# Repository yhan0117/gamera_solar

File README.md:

<!--
Hey, thanks for using the awesome-readme-template template.  
If you have any enhancements, then fork this project and create a pull request 
or just open an issue with the label "enhancement".

Don't forget to give this project a star for additional support ;)
Maybe you can mention me or this repo in the acknowledgements too
-->
<div align="center">

  <h1>Gamera Solar</h1>
  
  <p>
    An awesome README template for your projects! 
  </p>

<!-- Badges -->

<!-- Table of Contents -->
# :notebook_with_decorative_cover: Table of Contents

- [About the Project](#star2-about-the-project)
  * [Screenshots](#camera-screenshots)
  * [Tech Stack](#space_invader-tech-stack)
  * [Features](#dart-features)
  * [Color Reference](#art-color-reference)
  * [Environment Variables](#key-environment-variables)
- [Getting Started](#toolbox-getting-started)
  * [Prerequisites](#bangbang-prerequisites)
  * [Installation](#gear-installation)
  * [Running Tests](#test_tube-running-tests)
  * [Run Locally](#running-run-locally)
  * [Deployment](#triangular_flag_on_post-deployment)
- [Usage](#eyes-usage)
- [Roadmap](#compass-roadmap)
- [Contributing](#wave-contributing)
  * [Code of Conduct](#scroll-code-of-conduct)
- [FAQ](#grey_question-faq)
- [License](#warning-license)
- [Contact](#handshake-contact)
- [Acknowledgements](#gem-acknowledgements)

<!-- About the Project -->
## :star2: About the Project

<!-- Screenshots -->
### :camera: Screenshots

<div align="center"> 
  
</div>

<!-- TechStack -->
### :space_invader: Tech Stack

<details>
  <summary>Client</summary>
  <ul>
    <li><a href="https://www.typescriptlang.org/">Typescript</a></li>
    <li><a href="https://nextjs.org/">Next.js</a></li>
    <li><a href="https://reactjs.org/">React.js</a></li>
    <li><a href="https://tailwindcss.com/">TailwindCSS</a></li>
  </ul>
</details>

<details>
  <summary>Server</summary>
  <ul>
    <li><a href="https://www.typescriptlang.org/">Typescript</a></li>
    <li><a href="https://expressjs.com/">Express.js</a></li>
    <li><a href="https://go.dev/">Golang</a></li>
    <li><a href="https://nestjs.com/">Nest.js</a></li>
    <li><a href="https://socket.io/">SocketIO</a></li>
    <li><a href="https://www.prisma.io/">Prisma</a></li>    
    <li><a href="https://www.apollographql.com/">Apollo</a></li>
    <li><a href="https://graphql.org/">GraphQL</a></li>
  </ul>
</details>

<details>
<summary>Database</summary>
  <ul>
    <li><a href="https://www.mysql.com/">MySQL</a></li>
    <li><a href="https://www.postgresql.org/">PostgreSQL</a></li>
    <li><a href="https://redis.io/">Redis</a></li>
    <li><a href="https://neo4j.com/">Neo4j</a></li>
    <li><a href="https://www.mongodb.com/">MongoDB</a></li>
  </ul>
</details>

<details>
<summary>DevOps</summary>
  <ul>
    <li><a href="https://www.docker.com/">Docker</a></li>
    <li><a href="https://www.jenkins.io/">Jenkins</a></li>
    <li><a href="https://circleci.com/">CircleCLI</a></li>
  </ul>
</details>

<!-- Features -->
### :dart: Features

- Feature 1
- Feature 2
- Feature 3

<!-- Color Reference -->
### :art: Color Reference

| Color             | Hex                                                                |
| ----------------- | ------------------------------------------------------------------ |
| Primary Color |  #222831 |
| Secondary Color |  #393E46 |
| Accent Color |  #00ADB5 |
| Text Color |  #EEEEEE |

<!-- Env Variables -->
### :key: Environment Variables

To run this project, you will need to add the following environment variables to your .env file

`API_KEY`

`ANOTHER_API_KEY`

<!-- Getting Started -->
## 	:toolbox: Getting Started

<!-- Prerequisites -->
### :bangbang: Prerequisites

This project uses Yarn as package manager

```bash
 npm install --global yarn
```

<!-- Installation -->
### :gear: Installation

Install my-project with npm

```bash
  yarn install my-project
  cd my-project
```
   
<!-- Running Tests -->
### :test_tube: Running Tests

To run tests, run the following command

```bash
  yarn test test
```

<!-- Run Locally -->
### :running: Run Locally

Clone the project

```bash
  git clone https://github.com/Louis3797/awesome-readme-template.git
```

Go to the project directory

```bash
  cd my-project
```

Install dependencies

```bash
  yarn install
```

Start the server

```bash
  yarn start
```

<!-- Deployment -->
### :triangular_flag_on_post: Deployment

To deploy this project run

```bash
  yarn deploy
```

<!-- Usage -->
## :eyes: Usage

Use this space to tell a little more about your project and how it can be used. Show additional screenshots, code samples, demos or link to other resources.

```javascript
import Component from 'my-project'

function App() {
  return <Component />
}
```

<!-- Roadmap -->
## :compass: Roadmap

* [x] Todo 1
* [ ] Todo 2

<!-- Contributing -->
## :wave: Contributing

Contributions are always welcome!

See `contributing.md` for ways to get started.

<!-- Code of Conduct -->
### :scroll: Code of Conduct

Please read the [Code of Conduct](https://github.com/Louis3797/awesome-readme-template/blob/master/CODE_OF_CONDUCT.md)

<!-- FAQ -->
## :grey_question: FAQ

- Question 1

  + Answer 1

- Question 2

  + Answer 2

<!-- License -->
## :warning: License

Distributed under the no License. See LICENSE.txt for more information.

<!-- Contact -->
## :handshake: Contact

Your Name - [@twitter_handle](https://twitter.com/twitter_handle) - email@email_client.com

Project Link: [https://github.com/Louis3797/awesome-readme-template](https://github.com/Louis3797/awesome-readme-template)

<!-- Acknowledgments -->
## :gem: Acknowledgements

Use this section to mention useful resources and libraries that you have used in your projects.

 - [Shields.io](https://shields.io/)
 - [Awesome README](https://github.com/matiassingers/awesome-readme)
 - [Emoji Cheat Sheet](https://github.com/ikatyang/emoji-cheat-sheet/blob/master/README.md#travel--places)
 - [Readme Template](https://github.com/othneildrew/Best-README-Template)

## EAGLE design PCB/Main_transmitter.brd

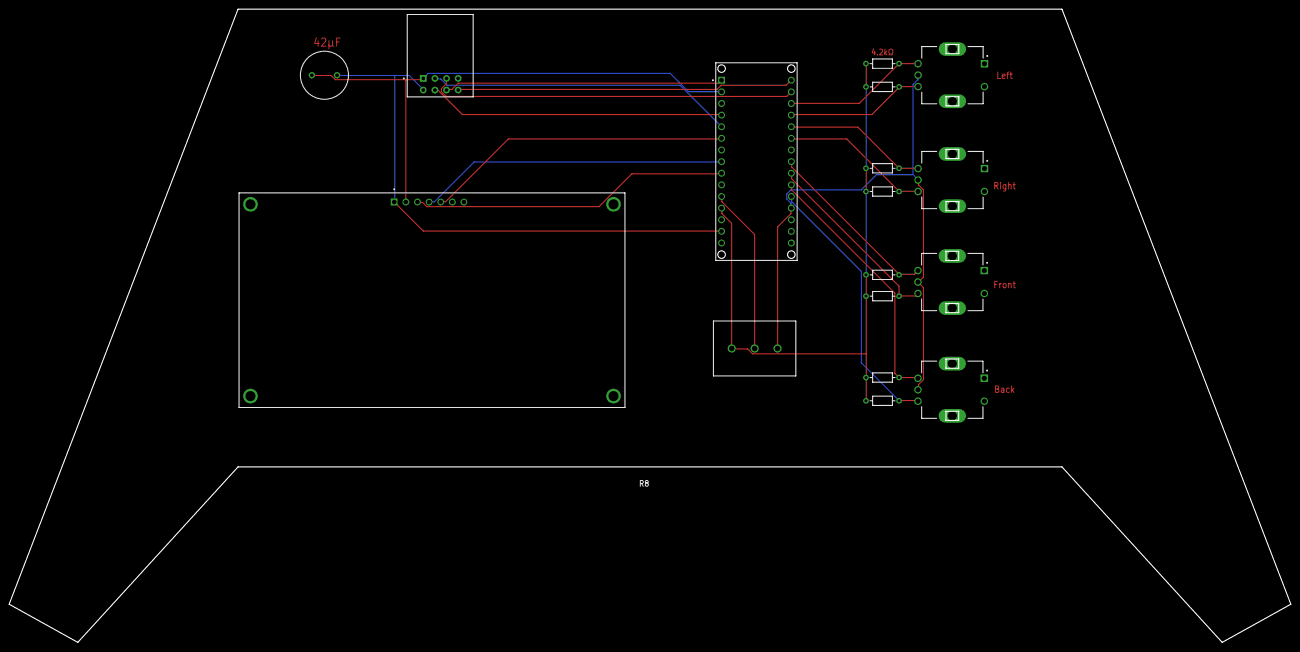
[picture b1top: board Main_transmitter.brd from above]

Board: 2 copper layers, 280.0 x 138.3 mm, 17 parts (0 on the bottom side), 21 nets.

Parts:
42MUF: CAPRD550W60D1025H1250B
B: ENCODER; XDCR_PEC11R-4215F-S0024
DS1: OLED
F: ENCODER; XDCR_PEC11R-4215F-S0024
L: ENCODER; XDCR_PEC11R-4215F-S0024
POT: POTENTIOMETER; P160
R: ENCODER; XDCR_PEC11R-4215F-S0024
R1, R2, R3, R4, R5, R6, R7, R8: R-US_AXIAL-7.2MM-PITCH; RESAD724W46L381D178B
U1: ARDUINONANO; NANO
U2: NRF24L01

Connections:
unnamed: L.A, R1.2, U1.28
unnamed: L.B, R2.2, U1.27
unnamed: R.A, R3.2, U1.26
unnamed: R.B, R4.2, U1.25
unnamed: F.A, R5.2, U1.23
unnamed: U1.4, U2.6
unnamed: F.B, R6.2, U1.22
unnamed: U1.5, U2.2
unnamed: B.A, R7.2, U1.21
unnamed: B.B, R8.2, U1.20
unnamed: B.COM, F.COM, L.COM, POT.3, R.COM, U1.19
unnamed: U1.30, U2.8
unnamed: U1.29, U2.3
unnamed: POT.2, U1.11
unnamed: DS1.3, U1.9
unnamed: DS1.4, U1.8
unnamed: 42MUF.1, DS1.2, U1.2, U2.1
unnamed: 42MUF.2, DS1.1, U1.14, U2.5
unnamed: U1.1, U2.7
unnamed: DS1.5, U1.6
unnamed: POT.1, R1.1, R2.1, R3.1, R4.1, R5.1, R6.1, R7.1, R8.1, U1.12

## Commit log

2022-11-15 Rename OutdoorBBR.ino to hardware/OutdoorBBR.ino
2022-11-15 Rename FourMotorTesting.ino to hardware/FourMotorTesting.ino
2022-11-15 Rename Wireless+controller.sch to Main_transmitter.sch
2022-11-15 Rename Main_transmitter.sch to PCB/Main_transmitter.sch
2022-11-15 Rename Wireless+controller.brd to Main_transmitter.brd
2023-06-05 Update BBR file
2023-08-28 reorganize project
2023-08-29 Update LICENSE
2023-09-05 add previous flight test files
2023-09-06 upload radio files
2023-09-18 update structural asm
2023-09-18 updated team logo
2023-09-21 updated master cad
